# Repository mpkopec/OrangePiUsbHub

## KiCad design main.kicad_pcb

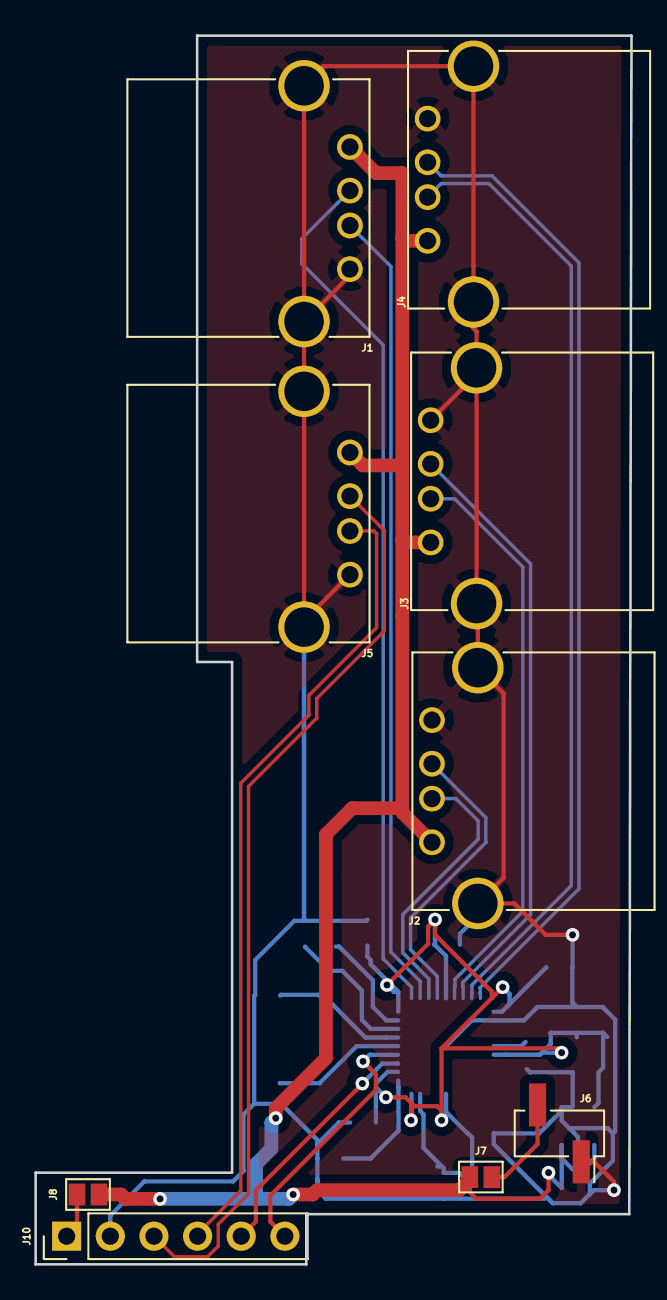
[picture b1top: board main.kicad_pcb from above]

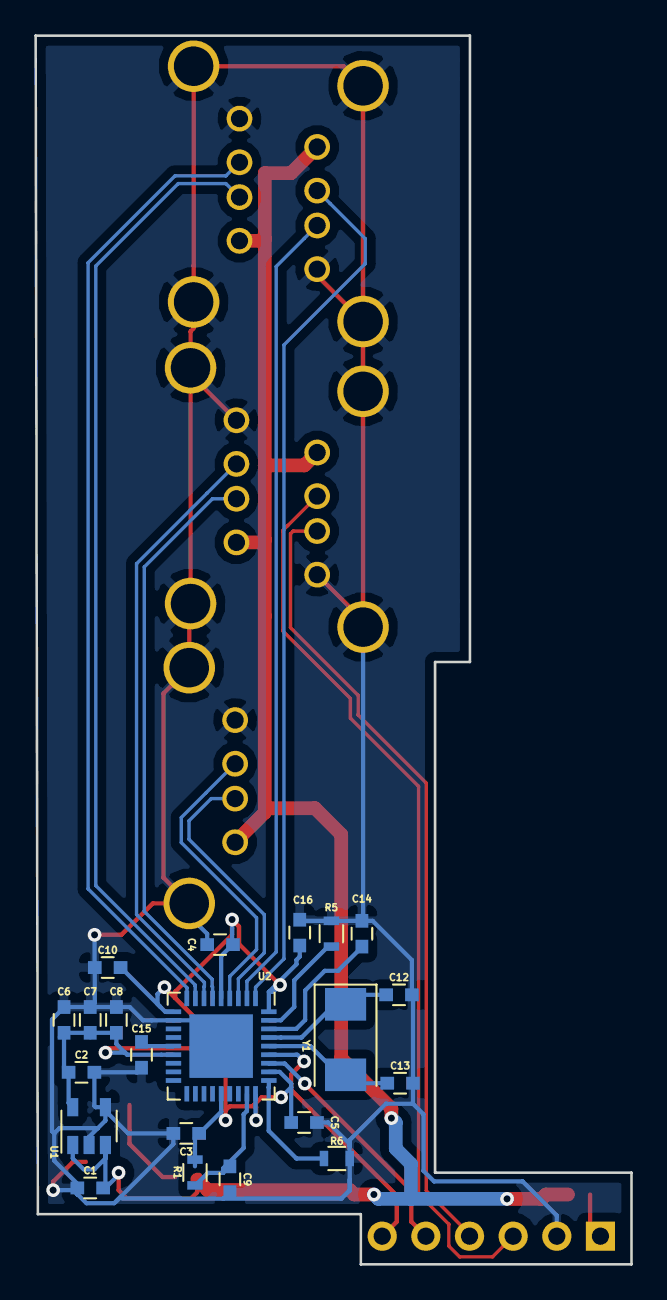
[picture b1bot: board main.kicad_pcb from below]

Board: 2 copper layers, 34.7 x 71.5 mm, 30 parts (21 on the bottom side), 24 nets.

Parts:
C1, C2, C3, C4, C5, C6, C7, C10, C16: 100n; C_0603
C8: 4.7u; C_0603
C9: 0,1uF; C_0603
C12, C13: 18p; C_0603
C14, C15: 0,1u; C_0603
J1, J2, J3, J4, J5: USB_A; UCCB_outline
J6: Conn_01x02; Pin_Header_Straight_1x02_Pitch2.54mm_SMD_Pin1Right
J7, J8: GS2
J10: OrangePiCon; Pin_Header_Straight_1x06_Pitch2.54mm
R1, R6: 100k; R_0603
R5: 12k(1%); R_0603
U1: MIC5504-3.3YM5; SOT-23-5
U2: USB2514B_Bi; QFN-36-1EP_6x6mm_Pitch0.5mm
Y1: 25MHz/50ppm; Crystal_SMD_Abracon_ABM3-2pin_5.0x3.2mm

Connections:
+3V3: C2.2, C3.1, C4.1, C5.1, C6.1, C7.1, C8.1, C10.1, C16.1, R1.1, U1.5, U2.5, U2.10, U2.15, U2.23, U2.27, U2.29, U2.36
+5V: C1.2, J1.1, J2.1, J3.1, J4.1, J5.1, J7.1, J8.2, U1.1, U1.3
GND: C1.1, C2.1, C3.2, C4.2, C5.2, C6.2, C7.2, C8.2, C9.1, C10.2, C12.2, C13.2, C14.1, C15.1, C16.2, J1.4, J1.5, J2.4, J2.5, J3.4, J3.5, J4.4, J4.5, J5.4, J5.5, J6.1, J10.2, R5.2, R6.2, U1.2, U1.4, U2.11, U2.37
unnamed: C9.2, R1.2, U2.26
unnamed: C12.1, U2.33, Y1.1
unnamed: C13.1, U2.32, Y1.2
unnamed: C14.2, U2.34
unnamed: C15.2, U2.14
unnamed: J6.2, J7.2
unnamed: J8.1, J10.1
unnamed: R5.1, U2.35
unnamed: R6.1, U2.28
USB1+: J1.3, U2.2
USB1-: J1.2, U2.1
USB2+: J2.3, U2.4
USB2-: J2.2, U2.3
USB3+: J3.3, U2.7
USB3-: J3.2, U2.6
USB4+: J4.3, U2.9
USB4-: J4.2, U2.8
USB5+: J5.3, J10.4
USB5-: J5.2, J10.3
USB_UP+: J10.6, U2.31
USB_UP-: J10.5, U2.30

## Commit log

2019-02-27 Init
2019-03-02 Layout update
2019-03-07 Layout draft 1
2019-03-27 First commit, fixed schematic, started work.
2019-03-27 Added hierarchial sheets for the input from the Pi and for output USB A connectors.
